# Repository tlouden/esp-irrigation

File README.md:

# ESP-Irrigation
Controlling irrigation with Home Assistant and Node Red using an ESP01 with ESP Home for Home Assistant.

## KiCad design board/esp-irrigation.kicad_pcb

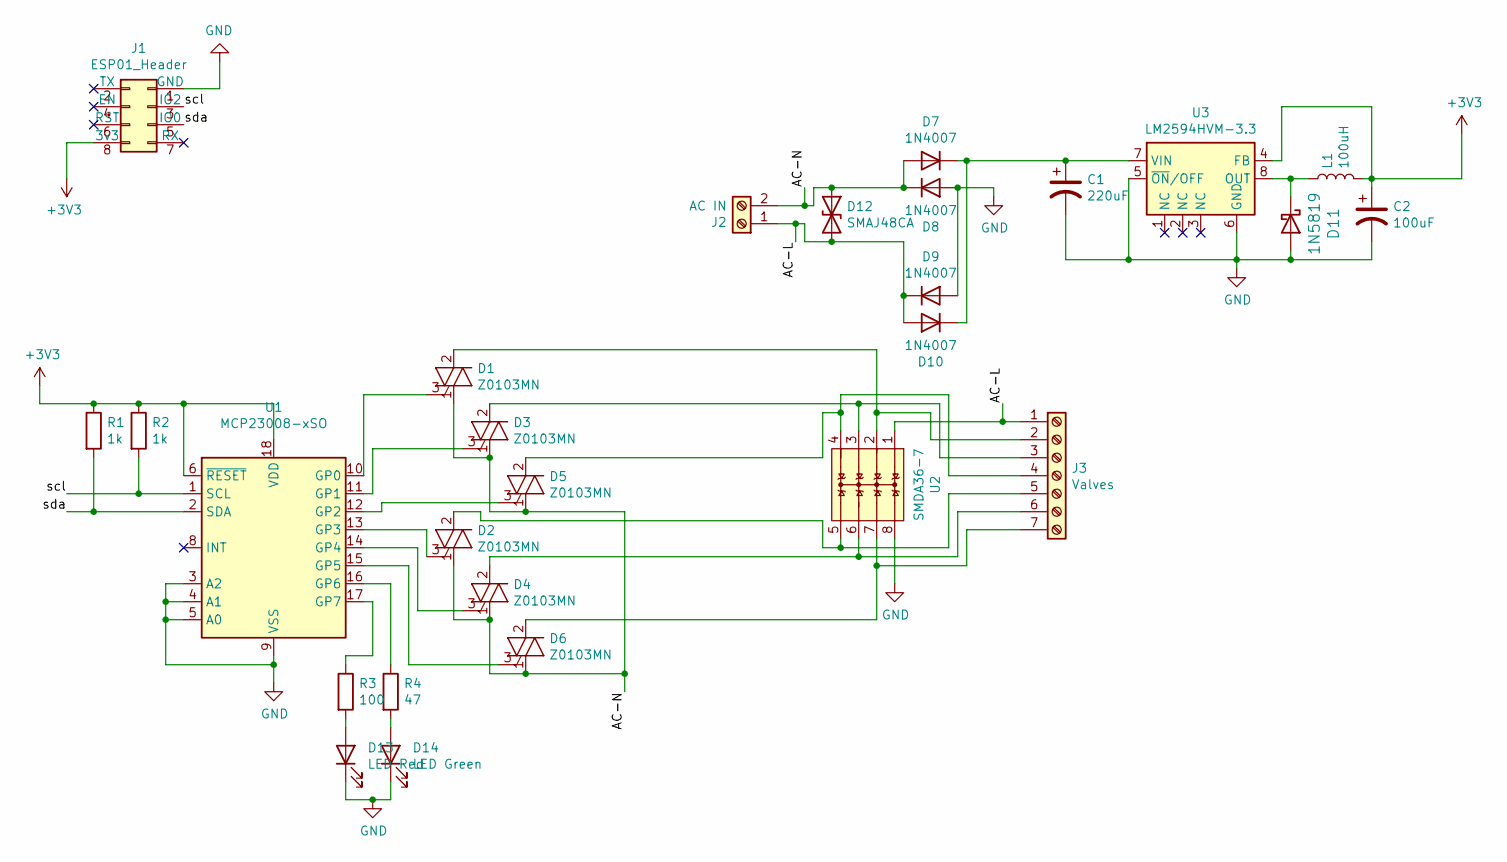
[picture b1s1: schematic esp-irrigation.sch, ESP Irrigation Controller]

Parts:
C1: 220uF; CP_Radial_D10.0mm_P5.00mm
C2: 100uF; CP_Elec_5x5.8
D1, D2, D3, D4, D5, D6: Z0103MN; SOT-223
D7, D8, D9, D10: 1N4007; D_DO-41_SOD81_P10.16mm_Horizontal
D11: 1N5819; D_DO-41_SOD81_P10.16mm_Horizontal; MPN 1N5819; Digi-Key_PN 1N5819FSCT-ND
D12: SMAJ48CA; D_SMA_Handsoldering
D13: LED Red; LED_D3.0mm
D14: LED Green; LED_D3.0mm
J1: ESP01_Header; PinSocket_2x04_ESP01
J2: AC IN; TerminalBlock_Phoenix_PT-1,5-2-5.0-H_1x02_P5.00mm_Horizontal
J3: Valves; TerminalBlock_Phoenix_PT-1,5-7-5.0-H_1x07_P5.00mm_Horizontal
L1: 100uH; L_Bourns_SRN6045TA
R1, R2: 1k; R_0805_2012Metric_Pad1.20x1.40mm_HandSolder
R3: 100; R_0805_2012Metric_Pad1.20x1.40mm_HandSolder
R4: 47; R_0805_2012Metric_Pad1.20x1.40mm_HandSolder
U1: MCP23008-xSO; SOIC-18W_7.5x11.6mm_P1.27mm
U2: SMDA36-7; SOIC-8_3.9x4.9mm_P1.27mm
U3: LM2594HVM-3.3; DIP-8_W7.62mm

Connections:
+3V3: C2.1, J1.8 (3v3), L1.2, R1.1, R2.1, U1.6 (~RESET), U1.18 (VDD), U3.4 (FB)
/AC-L: D9.1 (K), D10.2 (A), D12.2 (A2), J2.1, J3.1, U2.1
/AC-N: D1.1 (A1), D2.1 (A1), D3.1 (A1), D4.1 (A1), D5.1 (A1), D6.1 (A1), D7.2 (A), D8.1 (K), D12.1 (A1), J2.2
/scl: J1.3 (IO2), R2.2, U1.1 (SCL)
/sda: J1.5 (IO0), R1.2, U1.2 (SDA)
GND: C1.2, C2.2, D8.2 (A), D9.2 (A), D11.2 (A), D13.1 (K), D14.1 (K), J1.1 (GND), U1.3 (A2), U1.4 (A1), U1.5 (A0), U1.9 (VSS), U2.8, U3.5 (~ON~/OFF), U3.6 (GND)
unnamed: C1.1, D7.1 (K), D10.1 (K), U3.7 (VIN)
unnamed: D1.2 (A2), D1.4 (A4), J3.2, U2.2
unnamed: D1.3 (G), U1.10 (GP0)
unnamed: D2.2 (A2), D2.4 (A4), J3.5, U2.5
unnamed: D2.3 (G), U1.13 (GP3)
unnamed: D3.2 (A2), D3.4 (A4), J3.3, U2.3
unnamed: D3.3 (G), U1.11 (GP1)
unnamed: D4.2 (A2), D4.4 (A4), J3.6, U2.6
unnamed: D4.3 (G), U1.14 (GP4)
unnamed: D5.2 (A2), D5.4 (A4), J3.4, U2.4
unnamed: D5.3 (G), U1.12 (GP2)
unnamed: D6.2 (A2), D6.4 (A4), J3.7, U2.7
unnamed: D6.3 (G), U1.15 (GP5)
unnamed: D11.1 (K), L1.1, U3.8 (OUT)
unnamed: D13.2 (A), R3.2
unnamed: D14.2 (A), R4.2
unnamed: R3.1, U1.17 (GP7)
unnamed: R4.1, U1.16 (GP6)

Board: 2 copper layers, 27 parts (0 on the bottom side), 24 nets, no tracks yet.

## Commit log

2022-06-25 initial commit
    board WIP
2022-06-25 add indicator leds
